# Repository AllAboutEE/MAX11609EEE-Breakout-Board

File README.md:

# MAX11609EEE-Breakout-Board
A breakout board project for MAX11609EEE A/D multiplexer.

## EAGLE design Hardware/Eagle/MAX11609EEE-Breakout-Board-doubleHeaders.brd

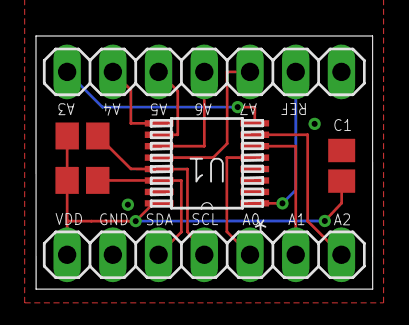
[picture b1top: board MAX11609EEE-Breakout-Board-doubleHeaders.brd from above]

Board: 2 copper layers, 18.7 x 14.1 mm, 6 parts (0 on the bottom side), 13 nets.

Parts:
C1: 0.1uF; C0805
JP2, JP4: 1X07
R1, R2: 4.7k; R0805
U1: MAX11609EEE+; 21-0055H_16

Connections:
AIN0: JP2.5, U1.5
AIN1: JP2.6, U1.6
AIN2: JP2.7, U1.7
AIN3: JP4.1, U1.8
AIN4: JP4.2, U1.9
AIN5: JP4.3, U1.10
AIN6: JP4.4, U1.11
AIN7: JP4.5, U1.12
GND: C1.2, JP2.2, U1.15
REF: JP4.6, U1.1
SCL: JP2.4, R2.1, U1.13
SDA: JP2.3, R1.1, U1.14
VDD: C1.1, JP2.1, R1.2, R2.2, U1.16

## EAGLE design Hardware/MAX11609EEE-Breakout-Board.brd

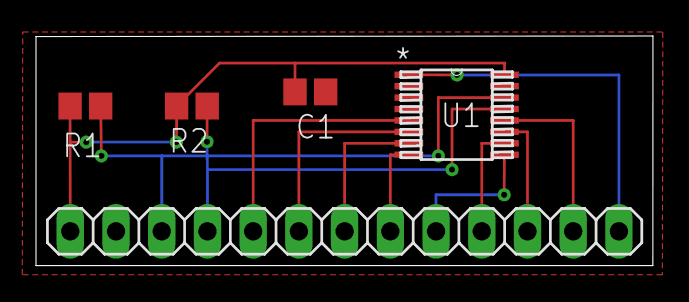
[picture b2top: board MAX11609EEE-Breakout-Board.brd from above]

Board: 2 copper layers, 34.3 x 12.8 mm, 5 parts (0 on the bottom side), 13 nets.

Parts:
C1: 0.1uF; C0805
JP3: 1X13
R1, R2: 4.7k; R0805
U1: MAX11609EEE+; 21-0055H_16

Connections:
AIN0: JP3.5, U1.5
AIN1: JP3.6, U1.6
AIN2: JP3.7, U1.7
AIN3: JP3.8, U1.8
AIN4: JP3.9, U1.9
AIN5: JP3.10, U1.10
AIN6: JP3.11, U1.11
AIN7: JP3.12, U1.12
GND: C1.2, JP3.2, U1.15
REF: JP3.13, U1.1
SCL: JP3.4, R2.1, U1.13
SDA: JP3.3, R1.1, U1.14
VDD: C1.1, JP3.1, R1.2, R2.2, U1.16

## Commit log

2015-05-25 Added schematic and board/pcb files.
2015-05-25 Moved license to software folder.
2015-05-25 Added library header and src files. Added datasheet pdf file. Added slickedit project and workspace files.
2015-06-29 - Added examples. - Code compiles but needs testing.
2015-06-29 - Tested examples. - Examples "work": read_all_channels show that there is a voltage of about 0.4v in every AIN pin. - Need to check PCB file to see what the problem might be (if it's hardware relate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
2015-06-29 These are the files that were sent to OSHPARK
2015-06-29 Contains the .brd file used for OSHPARK
2015-06-29 Moved all Eagle files to a folder.
2015-06-29 Moved SlickEdit files to software folder.
2015-06-29 Added PDF schematic.
2015-07-24 Added pin specification which is needed for ESP8266.
2015-07-24 Moved Arduino library to "Arduino" folder.
2015-07-24 Added and removed comments.
2015-07-24 Added NodeMCU library.
2017-03-08 Fix bug where I was not shifting the setup byte so the REF constants were not working.
